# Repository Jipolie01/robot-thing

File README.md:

# robot-thing
 Trying to broaded my horizon by partially redesigning a humanoid robot, making a PCB and developing code to control it via the web

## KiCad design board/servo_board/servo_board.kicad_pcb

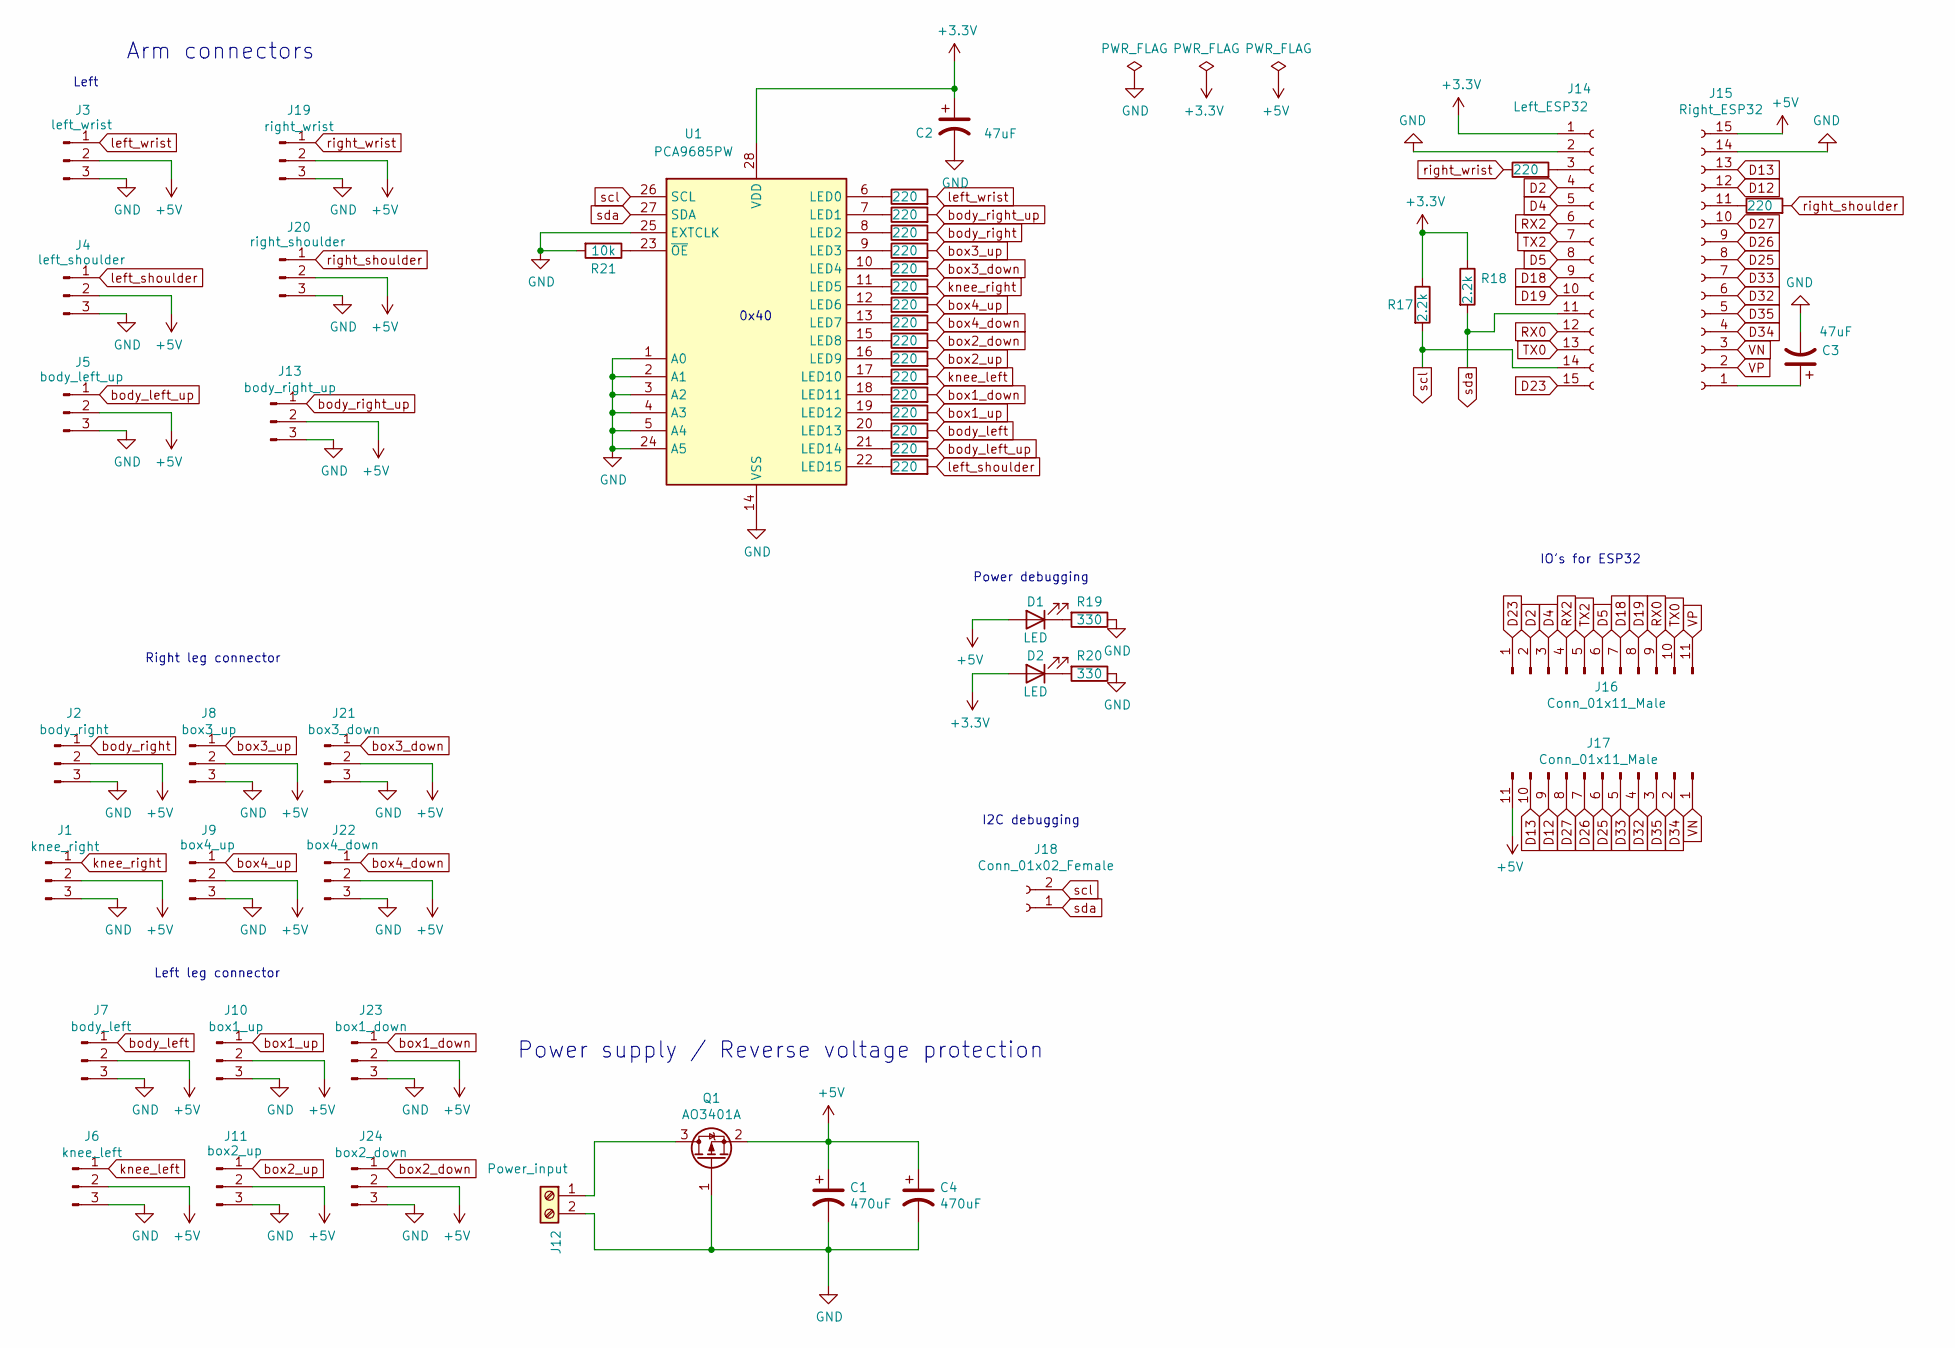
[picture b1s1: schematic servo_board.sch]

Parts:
C1, C4: 470uF; CP_Elec_6.3x7.7
C2, C3: 47uF; CP_Elec_5x5.4
D1, D2: LED; LED_1206_3216Metric
J1: knee_right; PinSocket_1x03_P2.54mm_Vertical
J2: body_right; PinSocket_1x03_P2.54mm_Vertical
J3: left_wrist; PinSocket_1x03_P2.54mm_Vertical
J4: left_shoulder; PinSocket_1x03_P2.54mm_Vertical
J5: body_left_up; PinSocket_1x03_P2.54mm_Vertical
J6: knee_left; PinSocket_1x03_P2.54mm_Vertical
J7: body_left; PinSocket_1x03_P2.54mm_Vertical
J8: box3_up; PinSocket_1x03_P2.54mm_Vertical
J9: box4_up; PinSocket_1x03_P2.54mm_Vertical
J10: box1_up; PinSocket_1x03_P2.54mm_Vertical
J11: box2_up; PinSocket_1x03_P2.54mm_Vertical
J12: Power_input; PhoenixContact_MCV_1,5_2-G-3.81_1x02_P3.81mm_Vertical
J13: body_right_up; PinSocket_1x03_P2.54mm_Vertical
J14: Left_ESP32; PinHeader_1x15_P2.54mm_Vertical
J15: Right_ESP32; PinHeader_1x15_P2.54mm_Vertical
J16, J17: Conn_01x11_Male; PinHeader_1x11_P2.54mm_Vertical
J18: Conn_01x02_Female; PinHeader_1x02_P2.54mm_Vertical
J19: right_wrist; PinSocket_1x03_P2.54mm_Vertical
J20: right_shoulder; PinSocket_1x03_P2.54mm_Vertical
J21: box3_down; PinSocket_1x03_P2.54mm_Vertical
J22: box4_down; PinSocket_1x03_P2.54mm_Vertical
J23: box1_down; PinSocket_1x03_P2.54mm_Vertical
J24: box2_down; PinSocket_1x03_P2.54mm_Vertical
Q1: AO3401A; SOT-23
R1, R2, R3, R4, R5, R6, R7, R8, R9, R10, R11, R12, R13, R14, R15, R16, R22, R23: 220; R_1206_3216Metric_Pad1.30x1.75mm_HandSolder
R17, R18: 2.2k; R_1206_3216Metric_Pad1.30x1.75mm_HandSolder
R19, R20: 330; R_1206_3216Metric_Pad1.30x1.75mm_HandSolder
R21: 10k; R_1206_3216Metric_Pad1.30x1.75mm_HandSolder
U1: PCA9685PW; TSSOP-28_4.4x9.7mm_P0.65mm

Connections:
+3V3: C2.1, D2.2 (A), J14.1, R17.1, R18.1, U1.28 (VDD)
+5V: C1.1, C4.1, D1.2 (A), J1.2, J2.2, J3.2, J4.2, J5.2, J6.2, J7.2, J8.2, J9.2, J10.2, J11.2, J13.2, J15.15, J17.11, J19.2, J20.2, J21.2, J22.2, J23.2, J24.2, Q1.2 (S)
D2: J14.4, J16.2
D4: J14.5, J16.3
D5: J14.8, J16.6
D12: J15.12, J17.9
D13: J15.13, J17.10
D18: J14.9, J16.7
D19: J14.10, J16.8
D23: J14.15, J16.1
D25: J15.8, J17.6
D26: J15.9, J17.7
D27: J15.10, J17.8
D32: J15.6, J17.4
D33: J15.7, J17.5
D34: J15.4, J17.2
D35: J15.5, J17.3
GND: C1.2, C2.2, C3.2, C4.2, J1.3, J2.3, J3.3, J4.3, J5.3, J6.3, J7.3, J8.3, J9.3, J10.3, J11.3, J12.2, J13.3, J14.2, J15.14, J19.3, J20.3, J21.3, J22.3, J23.3, J24.3, Q1.1 (G), R19.1, R20.1, R21.2, U1.1 (A0), U1.2 (A1), U1.3 (A2), U1.4 (A3), U1.5 (A4), U1.14 (VSS), U1.24 (A5), U1.25 (EXTCLK)
unnamed: C3.1, J15.1
unnamed: D1.1 (K), R19.2
unnamed: D2.1 (K), R20.2
unnamed: J12.1, Q1.3 (D)
unnamed: J14.3, R22.2
unnamed: J15.11, R23.1
unnamed: R1.1, U1.8 (LED2)
unnamed: R2.1, U1.9 (LED3)
unnamed: R3.1, U1.7 (LED1)
unnamed: R4.1, U1.21 (LED14)
unnamed: R5.1, U1.11 (LED5)
unnamed: R6.1, U1.10 (LED4)
unnamed: R7.1, U1.6 (LED0)
unnamed: R8.1, U1.15 (LED8)
unnamed: R9.1, U1.12 (LED6)
unnamed: R10.1, U1.17 (LED10)
unnamed: R11.1, U1.20 (LED13)
unnamed: R12.1, U1.19 (LED12)
unnamed: R13.1, U1.13 (LED7)
unnamed: R14.1, U1.18 (LED11)
unnamed: R15.1, U1.16 (LED9)
unnamed: R16.1, U1.22 (LED15)
unnamed: R21.1, U1.23 (~OE)
RX0: J14.12, J16.9
RX2: J14.6, J16.4
TX0: J14.13, J16.10
TX2: J14.7, J16.5
VN: J15.3, J17.1
VP: J15.2, J16.11
body_left: J7.1, R11.2
body_left_up: J5.1, R4.2
body_right: J2.1, R1.2
body_right_up: J13.1, R3.2
box1_down: J23.1, R14.2
box1_up: J10.1, R12.2
box2_down: J24.1, R8.2
box2_up: J11.1, R15.2
box3_down: J21.1, R6.2
box3_up: J8.1, R2.2
box4_down: J22.1, R13.2
box4_up: J9.1, R9.2
knee_left: J6.1, R10.2
knee_right: J1.1, R5.2
left_shoulder: J4.1, R16.2
left_wrist: J3.1, R7.2
right_shoulder: J20.1, R23.2
right_wrist: J19.1, R22.1
scl: J14.14, J18.2, R17.2, U1.26 (SCL)
sda: J14.11, J18.1, R18.2, U1.27 (SDA)

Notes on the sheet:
Power supply / Reverse voltage protection
Arm connectors
Left leg connector
Right leg connector
Left
0x40
Power debugging
I2C debugging
IO's for ESP32

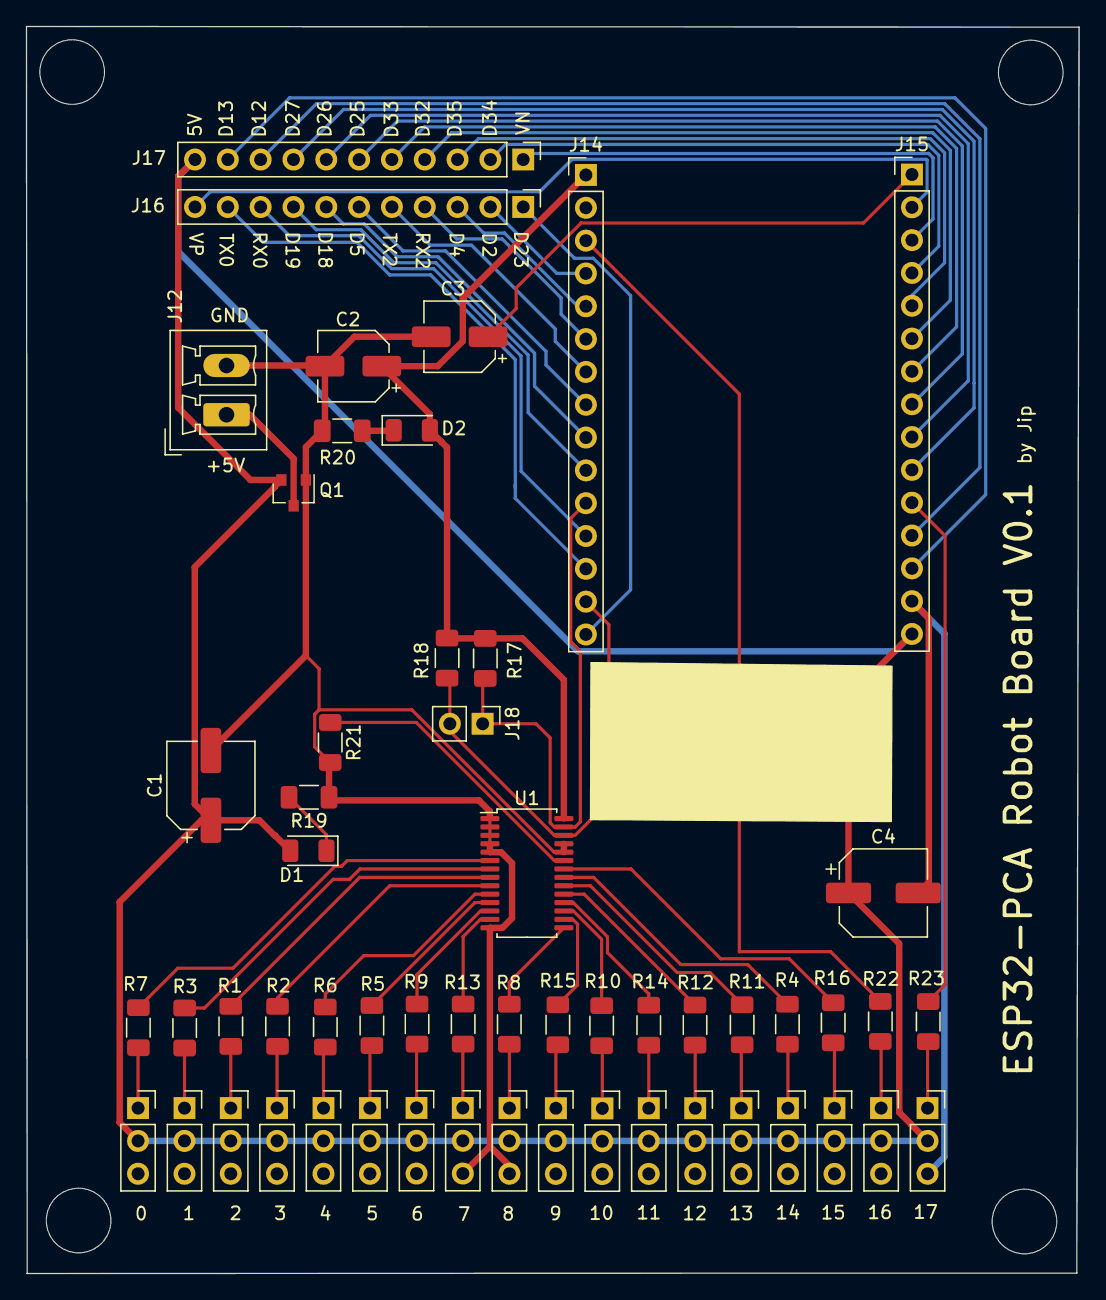
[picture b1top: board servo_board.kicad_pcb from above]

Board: 2 copper layers, 81.5 x 96.5 mm, 55 parts (0 on the bottom side), 67 nets.

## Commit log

2022-01-23 Current progress
2022-03-05 Adding flask architecture to send big batch of movements
2022-03-05 Adding ESP architecture to connect receive messages and add to queue
2022-03-05 Forgot to empty list when sending
2023-02-15 UpdatePCB gerber
